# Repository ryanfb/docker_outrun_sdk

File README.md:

# Docker Out Run SDK

This is a dockerized environment for running/using the [Out Run Arcade SDK](http://www.aaldert.com/outrun/sdk.html), since it was originally developed for Windows. It uses [my `m68k_gcc` Docker image](https://hub.docker.com/r/ryanfb/m68k_gcc/) for the cross-compiler toolchain, then builds the SDK from scratch inside that environment.

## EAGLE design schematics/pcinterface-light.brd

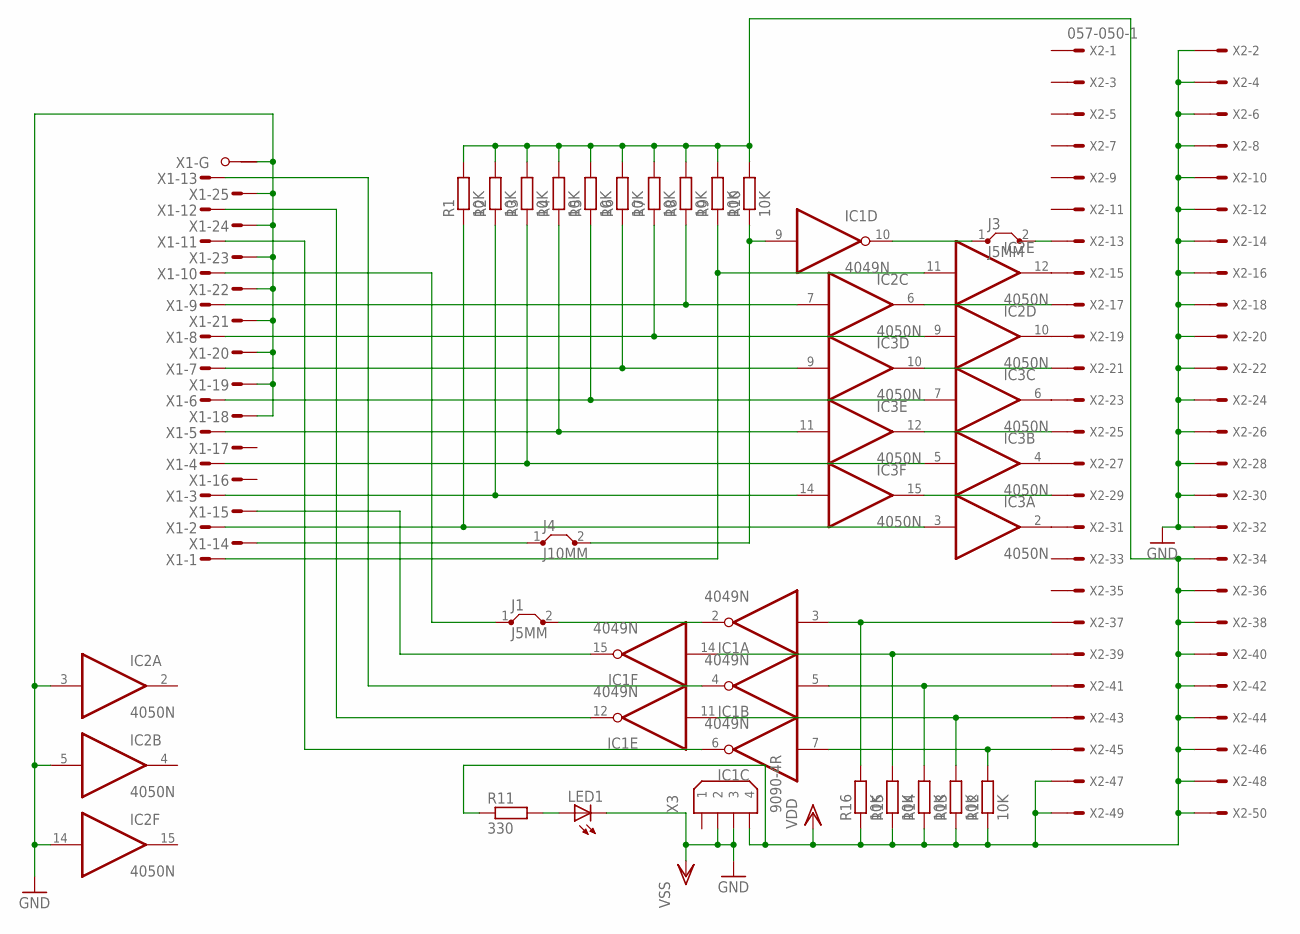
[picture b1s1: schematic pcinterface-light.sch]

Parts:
IC1: 4049N; DIL16
IC2, IC3: 4050N; DIL16
J1, J3: J5MM; 05
J4: J10MM; 10
LED1: LED3MM
R1, R2, R3, R4, R5, R6, R7, R8, R9, R10, R12, R13, R14, R15, R16: 10K; 0207/10
R11: 330; 0207/10
X1: M25HPS; M25HP
X2: 057-050-1
X3: 9090-4R

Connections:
unnamed: J4.1, X1.14 (M)
unnamed: LED1.A, R11.2
unnamed: IC2.12 (O), X2.15
unnamed: IC2.6 (O), X2.17
unnamed: IC2.10 (O), X2.19
unnamed: IC3.10 (O), X2.21
unnamed: IC3.6 (O), X2.23
unnamed: IC3.12 (O), X2.25
unnamed: IC3.4 (O), X2.27
unnamed: IC3.15 (O), X2.29
unnamed: IC3.2 (O), X2.31
unnamed: IC1.9 (I), J4.2, R10.1
unnamed: IC2.11 (I), R9.1, X1.1 (M)
unnamed: IC2.7 (I), R8.1, X1.9 (M)
unnamed: IC2.9 (I), R7.1, X1.8 (M)
unnamed: IC3.9 (I), R6.1, X1.7 (M)
unnamed: IC3.7 (I), R5.1, X1.6 (M)
unnamed: IC3.11 (I), R4.1, X1.5 (M)
unnamed: IC3.5 (I), R3.1, X1.4 (M)
unnamed: IC3.14 (I), R2.1, X1.3 (M)
unnamed: IC3.3 (I), R1.1, X1.2 (M)
unnamed: IC1.7 (I), R12.2, X2.45
unnamed: IC1.11 (I), R13.2, X2.43
unnamed: IC1.5 (I), R14.2, X2.41
unnamed: IC1.14 (I), R15.2, X2.39
unnamed: IC1.3 (I), R16.2, X2.37
unnamed: IC1.6 (O), X1.11 (M)
unnamed: IC1.12 (O), X1.12 (M)
unnamed: IC1.4 (O), X1.13 (M)
unnamed: IC1.15 (O), X1.15 (M)
unnamed: J1.1, X1.10 (M)
unnamed: IC1.2 (O), J1.2
unnamed: IC1.10 (O), J3.1
unnamed: J3.2, X2.13
VDD: IC1.1 (VDD), IC2.1 (VDD), IC3.1 (VDD), R1.2, R2.2, R3.2, R4.2, R5.2, R6.2, R7.2, R8.2, R9.2, R10.2, R11.1, R12.1, R13.1, R14.1, R15.1, R16.1, X2.34, X2.36, X2.38, X2.40, X2.42, X2.44, X2.46, X2.47, X2.48, X2.49, X2.50, X3.4
VSS: IC1.8 (VSS), IC2.3 (I), IC2.5 (I), IC2.8 (VSS), IC2.14 (I), IC3.8 (VSS), LED1.K (C), X1.18 (M), X1.19 (M), X1.20 (M), X1.21 (M), X1.22 (M), X1.23 (M), X1.24 (M), X1.25 (M), X1.G1, X2.2, X2.4, X2.6, X2.8, X2.10, X2.12, X2.14, X2.16, X2.18, X2.20, X2.22, X2.24, X2.26, X2.28, X2.30, X2.32, X3.2, X3.3

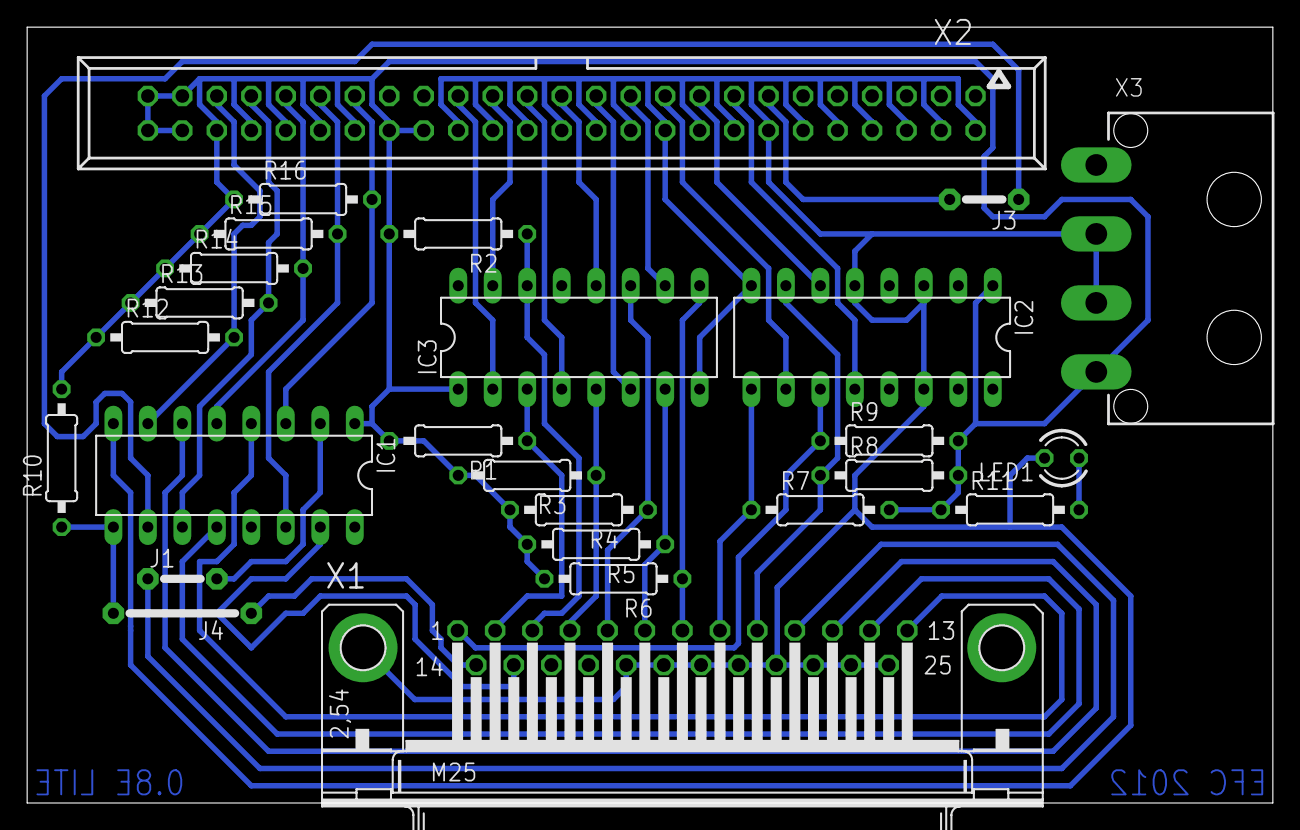
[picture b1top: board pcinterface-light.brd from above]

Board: 2 copper layers, 91.7 x 57.1 mm, 26 parts (0 on the bottom side), 36 nets.

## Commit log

2017-06-10 Initial snapshot from outrun_sdk_preview_2.zip, minus gcc directory
2017-06-10 Initial Dockerfile, build scripts, and MAME compat fix
2017-06-10 Add README
2017-06-10 Copy make.sh to other sample directories
